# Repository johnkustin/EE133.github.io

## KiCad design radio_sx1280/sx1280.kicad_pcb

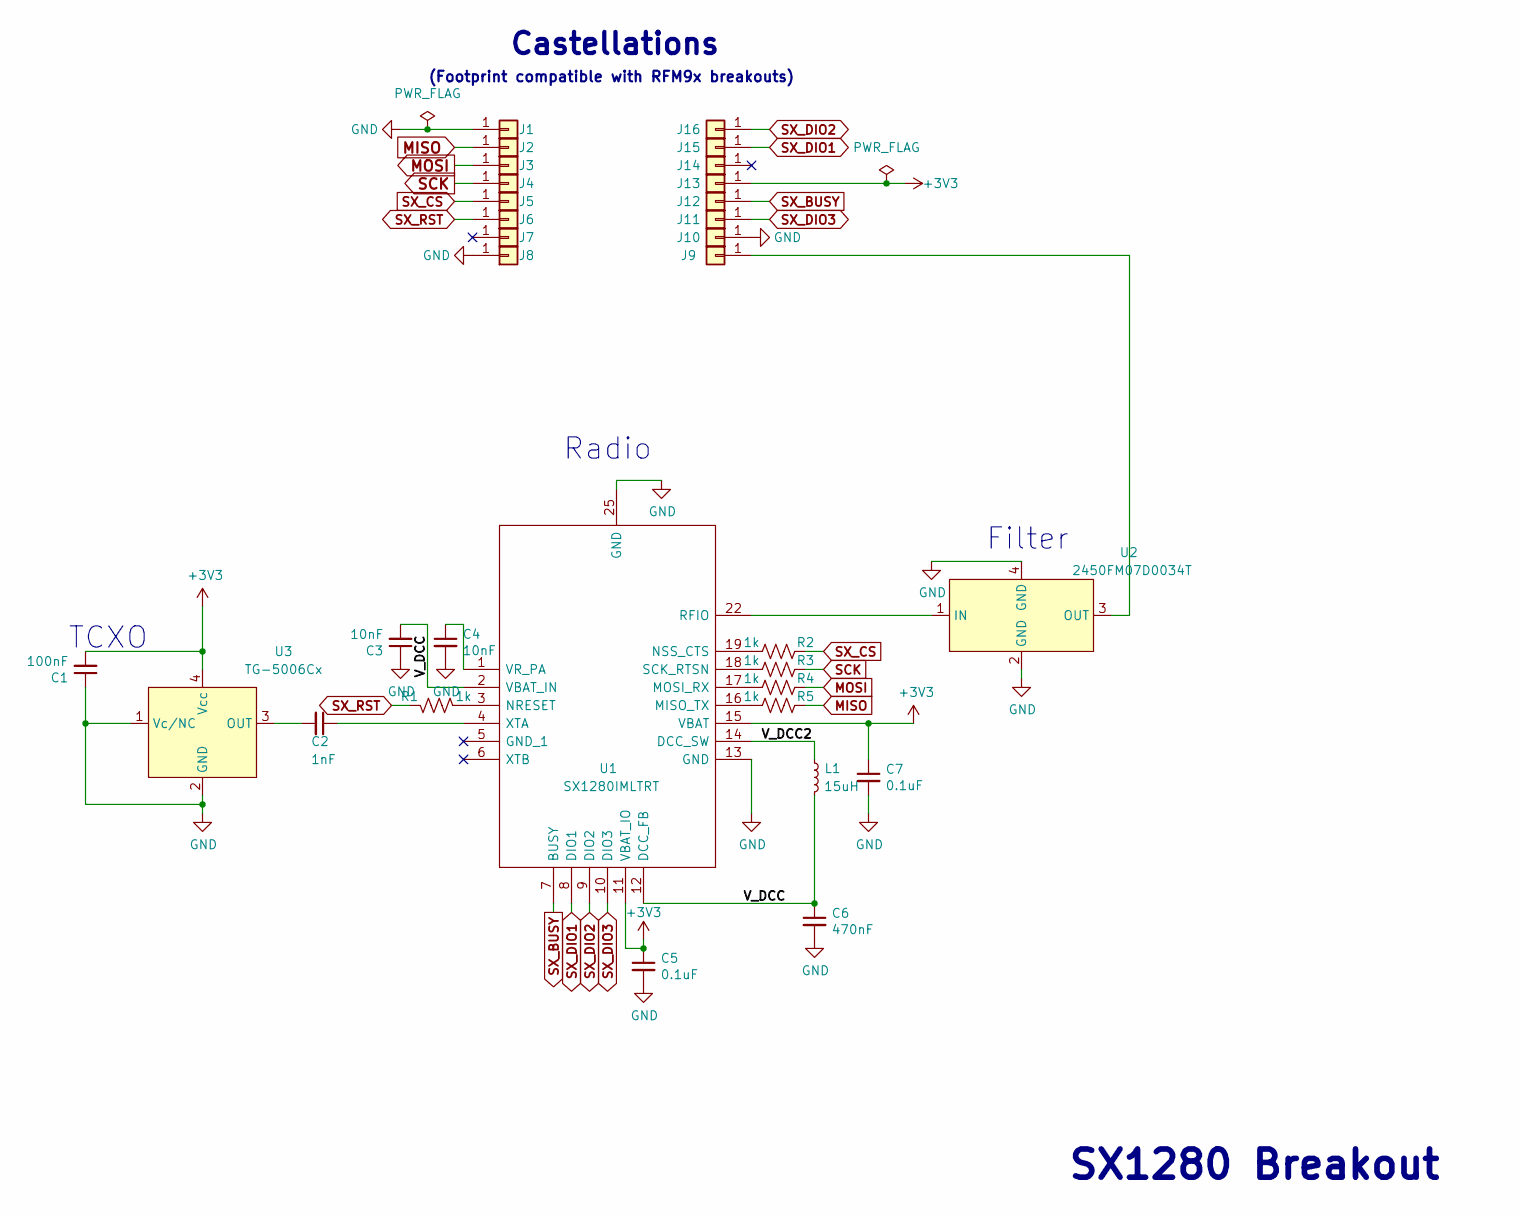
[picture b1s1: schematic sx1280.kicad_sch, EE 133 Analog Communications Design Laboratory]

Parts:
C1: 100nF; C_0402_1005Metric
C2: 1nF; C_0402_1005Metric
C3, C4: 10nF; C_0402_1005Metric
C5, C7: 0.1uF; C_0402_1005Metric
C6: 470nF; C_0402_1005Metric
J1, J2, J3, J4, J5, J6, J7, J8, J9, J10, J11, J12, J13, J14, J15, J16: Conn_01x01; castellated
L1: 15uH; L_0805_2012Metric
R1, R2, R3, R4, R5: 1k; R_0402_1005Metric
U1: SX1280IMLTRT; QFN50P400X400X80-25N-D; Manufacturer_Part_Number SX1280IMLTRT; Mouser Part Number 947-SX1280IMLTRT
U2: 2450FM07D0034T; Manufacturer_Part_Number 2450FM07D0034T; Mouser Part Number 609-2450FM07D0034T
U3: TG-5006Cx; Crystal_SMD_2520-4Pin_2.5x2.0mm

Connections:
+3V3: C1.2, C5.1, C7.1, J13.1, U1.11 (VBAT_IO), U1.15 (VBAT), U3.4 (Vcc)
/V_DCC: C3.2, C6.1, L1.2, U1.2 (VBAT_IN), U1.12 (DCC_FB)
/V_DCC2: L1.1, U1.14 (DCC_SW)
GND: C1.1, C3.1, C4.2, C5.2, C6.2, C7.2, J1.1, J8.1, J10.1, U1.13 (GND), U1.20 (GND), U1.21 (GND), U1.23 (GND), U1.24 (GND), U1.25 (GND), U2.2 (GND_1), U2.4 (GND_2), U3.1 (Vc/NC), U3.2 (GND)
MISO: J2.1, R5.1
MOSI: J3.1, R4.1
unnamed: C2.1, U1.4 (XTA)
unnamed: C2.2, U3.3 (OUT)
unnamed: C4.1, U1.1 (VR_PA)
unnamed: J9.1, U2.3 (OUT)
unnamed: R1.2, U1.3 (NRESET)
unnamed: R2.2, U1.19 (NSS_CTS)
unnamed: R3.2, U1.18 (SCK_RTSN)
unnamed: R4.2, U1.17 (MOSI_RX)
unnamed: R5.2, U1.16 (MISO_TX)
unnamed: U1.22 (RFIO), U2.1 (IN)
SCK: J4.1, R3.1
SX_BUSY: J12.1, U1.7 (BUSY)
SX_CS: J5.1, R2.1
SX_DIO1: J15.1, U1.8 (DIO1)
SX_DIO2: J16.1, U1.9 (DIO2)
SX_DIO3: J11.1, U1.10 (DIO3)
SX_RST: J6.1, R1.1

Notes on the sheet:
Castellations
SX1280 Breakout
Filter
TCXO
Radio
(Footprint compatible with RFM9x breakouts)

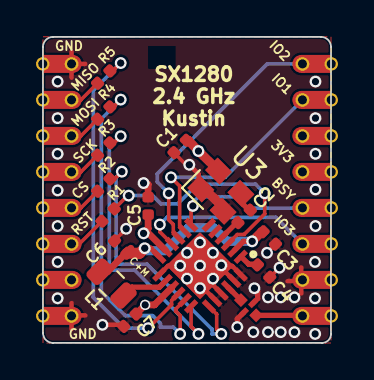
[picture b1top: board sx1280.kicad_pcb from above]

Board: 4 copper layers, 16.0 x 17.0 mm, 32 parts (0 on the bottom side), 23 nets.

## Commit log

2022-01-25 added sx1280, oscillator, and front end filter for sx1280
2022-01-26 schematic capture complete
2022-01-26 add decoupling cap to txco vdd
2022-01-26 tied a nc to ground for txco
2022-02-01 added project specific footprints
2022-02-01 schematic and layout
2022-02-03 added layer markings and annotated silk screen and gave 0.254mm clearance b/t inner layer copper plane and bord edge cut
2022-02-03 minor
2022-02-03 added Lab_1 folder
2022-02-03 add images for lab1 writeup
2022-02-06 ltspice sims
2022-02-06 ltspice sections done
2022-02-07 fixed edge cuts dupe
2022-02-07 new images for lab 1 and 2
2022-02-08 switching writeup to markdown. added new images
2022-02-08 added discussion
2022-02-08 done
2022-02-08 new images
2022-02-08 reformat eqns
2022-02-11 lab3 mixer images
2022-02-20 updated lab1 writeup according to feedback from lecture
2022-02-20 fixing links and background colors
2022-02-20 final
2022-02-21 initial commit for lab2writeup
2022-02-21 beginning section
2022-02-21 added figure
2022-02-21 fixed links
2022-02-21 added figures
2022-02-21 added scope pics. starting on discussion
2022-02-21 more discussion
2022-02-22 ready for review
2022-02-22 fixed figures
2022-02-26 init file writeup
2022-02-27 added figures and py script to make figures
2022-02-27 adding background
2022-02-28 discussion
2022-02-28 final review
2022-02-28 figure adjustments
